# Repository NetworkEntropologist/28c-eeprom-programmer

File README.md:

# 28c-eeprom-programmer

A parallel EEPROM programmer for the 28C family, built around an Arduino Nano. Simply drop an EEPROM into the ZIF socket, connect the Nano over USB, and burn a ROM image onto it from your computer.

If you've watched Ben Eater's 8-bit computer series, this will look familiar. That's where the idea came from. I wanted a proper PCB instead of the breadboard version, and a ZIF socket so I'm not bending chip pins every time I swap an EEPROM.

## About this project

This is a personal project that I'm putting it up in case someone else finds it useful or interesting. I'm not planning to write full documentation right now, and I might not ever get to it. So for the moment, the board files and the code are the documentation.

If you find a bug, or you get it working with a chip I haven't tested, feel free to open an issue or a pull request. Just don't expect a fast reply — this is a side thing I work on when I have time.

## Where this came from

For a number of years I have been interested in retrocomputing, when one day I stumbled across [Ben Eater's YouTube channel](https://www.youtube.com/@BenEater). Following his series on espeially the [6502 breadboard computer project](https://youtube.com/playlist?list=PLowKtXNTBypFbtuVMUVXNR0z1mu7dp7eH) I wanted to start building this for myself, or rather using this as inspiration to design and build my own 6501 computer, and this EEPROM Programmer seemed like the best place to start, as this would be a required tool for pretty much everything else. 

I have to mention at this point, two other related projects that I used heavily for both inspiration, as well as for insights into how other creators tackled this:

- **Ben Eater's [eeprom-programmer](https://github.com/beneater/eeprom-programmer)** — the one from his 8-bit computer series. Same core idea as mine: an Arduino driving the address lines through a pair of 74HC595 shift registers. If you've never seen it, watch his video first. He explains the whole thing better than I can here.
- **Erik van Zijst's [eeprom](https://github.com/erikvanzijst/eeprom)** — an Arduino Uno shield with a KiCad board and an interactive Python client. Seeing someone take the breadboard version and turn it into a proper PCB with host software was a big part of what pushed me to do my own board.

So thanks to both of them. My version borrows ideas from each and mixes in what I wanted out of it.

## Does it actually work?

Short answer? Yes. First test on the PCB, after soldering it, was to attempt burning a copy of Wozmon onto the IC, which checked out byte exact. Turns out Wozmon is a really great test, as the contents is very well known and documented all over the internet.

## What it does

- Writes a ROM image to a 28C-family EEPROM over USB serial
- Reads the chip back so you can verify the write

## Supported chips

Anything in the 28C family that follows the 28C64 pinout should work. That being said, I've only tested it with a 28C64 so far. So treat everything else as *should work* rather than *known good*. If you run it with a 28C16 or 28C256, I'd like to hear how it goes.

## Hardware / BOM

The main parts, leaving out the passives:

- 1x Arduino Nano driving the entire process
- 2x 74HC595 shift registers (serial in, parallel out) driving the address lines
- 1x 28-pin ZIF socket

## Repo layout

- `hardware/` — the full KiCad project (schematic and PCB)
- `firmware/` — the Arduino firmware for the Nano
- `software/` — the host-side Python that talks to the board

## Getting boards made

The KiCad project lives in `hardware/`. Open it in KiCad, export the Gerbers, and send them off to whichever fab you like. I used JLCPCB with a purple soldermask and had no trouble — DRC passed and the boards were fine.

## Flashing the firmware

The firmware in `firmware/` was written with [PlatformIO](https://platformio.org/), not the regular Arduino IDE. So the easiest way to build and upload is with PlatformIO (either the VS Code extension or the CLI). Open the `firmware/` folder as a PlatformIO project, plug in the Nano, and run the upload.

If you're using an older Nano clone, you may need to point the build at the old bootloader, otherwise the upload will fail. That's set in the `platformio.ini`.

This assumes you've used PlatformIO before. If you haven't, their [docs](https://docs.platformio.org/) cover installing it and uploading to a board better than I could here.

## Using the software

The host software is in `software/` and it's written in Python. Fair warning: it's still very much a work in progress. Because of that I'm not going to write down a fixed set of commands here that might change next week. Have a look in the `software/` folder and read the code to see how it works for now.

I'm planning to rewrite this side in Rust later on, so expect it to change.

## License

- Hardware (everything in `hardware/`): [CERN-OHL-S v2](https://ohwr.org/cern_ohl_s_v2.txt)
- Firmware and software (`firmware/` and `software/`): [MIT](https://opensource.org/licenses/MIT)

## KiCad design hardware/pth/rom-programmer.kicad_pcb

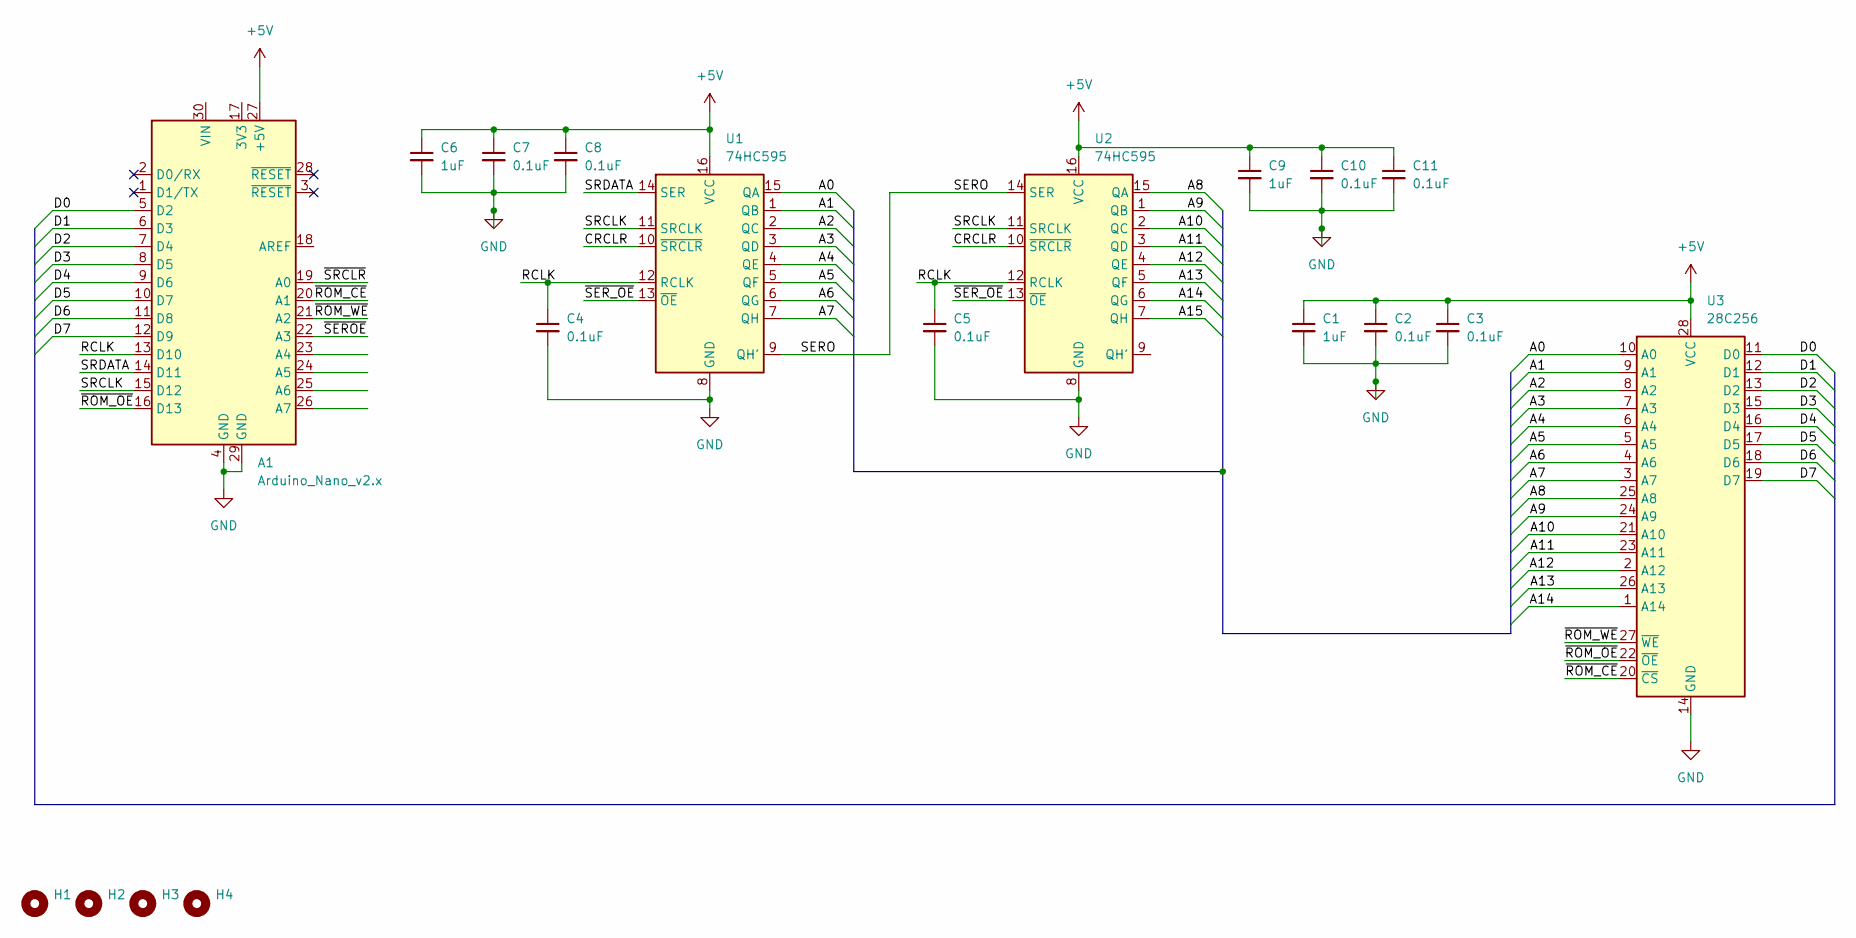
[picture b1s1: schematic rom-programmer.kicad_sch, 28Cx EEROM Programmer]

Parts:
A1: Arduino_Nano_v2.x; Arduino_Nano
C1, C6, C9: 1uF; C_Disc_D3.4mm_W2.1mm_P2.50mm; Mouser SKU 187-CL21B104KCFWPJF
C2, C3, C4, C5, C7, C8, C10, C11: 0.1uF; C_Disc_D3.4mm_W2.1mm_P2.50mm; Mouser SKU 187-CL05B104KO54PND
H1, H2, H3, H4: MountingHole; MountingHole_2.2mm_M2
U1, U2: 74HC595; DIP-16_W7.62mm_Socket; Mouser SKU 595-SN74HC595ANSR
U3: 28C256; DIP_Socket-28_W11.9mm_W12.7mm_W15.24mm_W17.78mm_W18.5mm_3M_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

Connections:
+5V: A1.27 (+5V), C1.1, C2.1, C3.1, C6.1, C7.1, C8.1, C9.1, C10.1, C11.1, U1.16 (VCC), U2.16 (VCC), U3.28 (VCC)
/A0: U1.15 (QA), U3.10 (A0)
/A1: U1.1 (QB), U3.9 (A1)
/A2: U1.2 (QC), U3.8 (A2)
/A3: U1.3 (QD), U3.7 (A3)
/A4: U1.4 (QE), U3.6 (A4)
/A5: U1.5 (QF), U3.5 (A5)
/A6: U1.6 (QG), U3.4 (A6)
/A7: U1.7 (QH), U3.3 (A7)
/A8: U2.15 (QA), U3.25 (A8)
/A9: U2.1 (QB), U3.24 (A9)
/A10: U2.2 (QC), U3.21 (A10)
/A11: U2.3 (QD), U3.23 (A11)
/A12: U2.4 (QE), U3.2 (A12)
/A13: U2.5 (QF), U3.26 (A13)
/A14: U2.6 (QG), U3.1 (A14)
/A15: U2.7 (QH)
/CRCLR: U1.10 (~SRCLR), U2.10 (~SRCLR)
/D0: A1.5 (D2), U3.11 (D0)
/D1: A1.6 (D3), U3.12 (D1)
/D2: A1.7 (D4), U3.13 (D2)
/D3: A1.8 (D5), U3.15 (D3)
/D4: A1.9 (D6), U3.16 (D4)
/D5: A1.10 (D7), U3.17 (D5)
/D6: A1.11 (D8), U3.18 (D6)
/D7: A1.12 (D9), U3.19 (D7)
/RCLK: A1.13 (D10), C4.1, C5.1, U1.12 (RCLK), U2.12 (RCLK)
/SERO: U1.9 (QH'), U2.14 (SER)
/SRCLK: A1.15 (D12), U1.11 (SRCLK), U2.11 (SRCLK)
/SRDATA: A1.14 (D11), U1.14 (SER)
/~ROM_CE: A1.20 (A1), U3.20 (~CS)
/~ROM_OE: A1.16 (D13), U3.22 (~OE)
/~ROM_WE: A1.21 (A2), U3.27 (~WE)
/~SEROE: A1.22 (A3)
/~SER_OE: U1.13 (~OE), U2.13 (~OE)
/~SRCLR: A1.19 (A0)
GND: A1.4 (GND), A1.29 (GND), C1.2, C2.2, C3.2, C4.2, C5.2, C6.2, C7.2, C8.2, C9.2, C10.2, C11.2, U1.8 (GND), U2.8 (GND), U3.14 (GND)

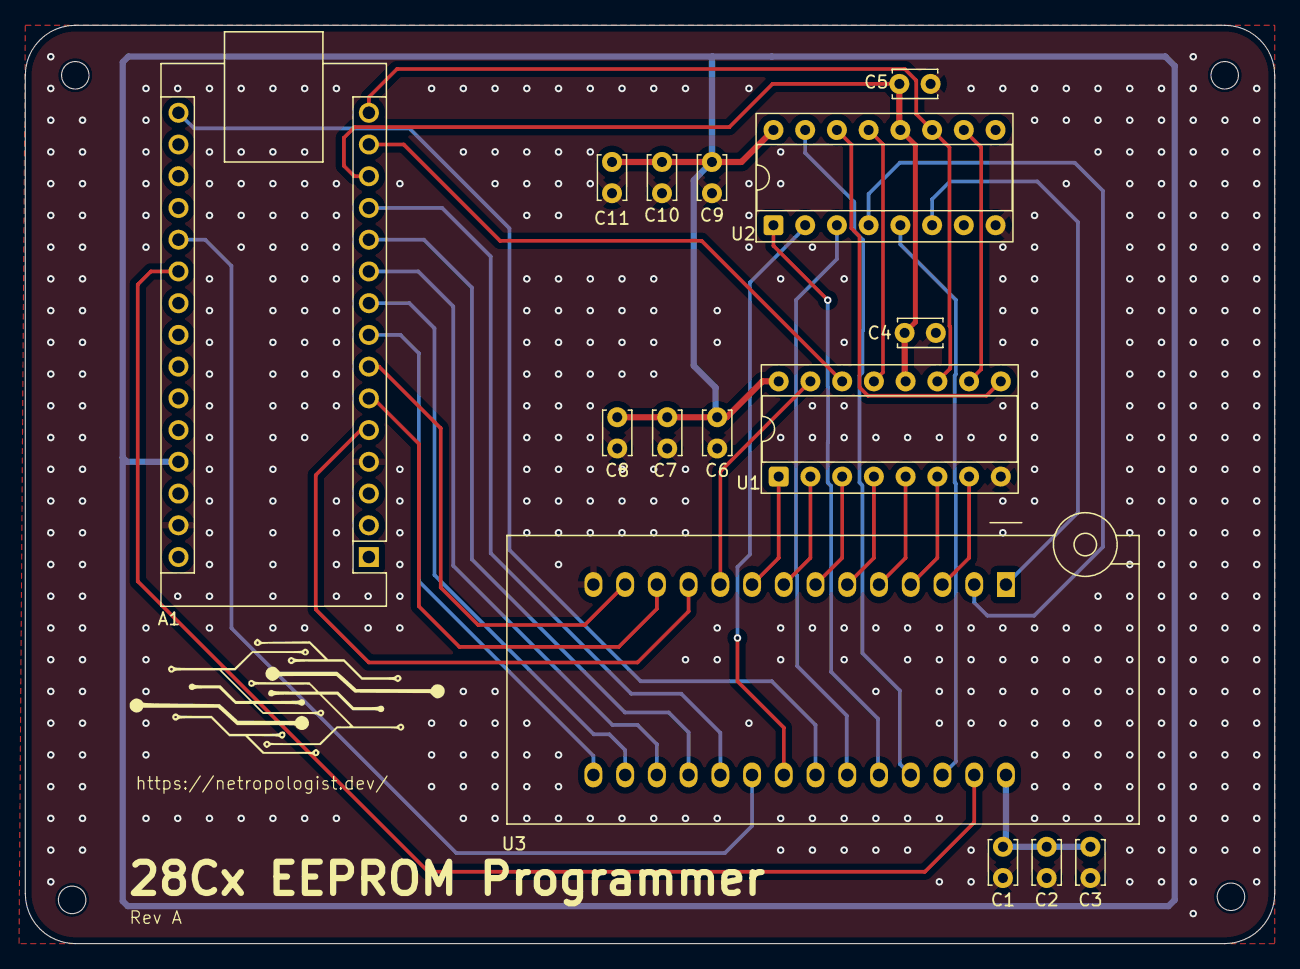
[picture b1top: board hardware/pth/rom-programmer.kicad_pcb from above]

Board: 2 copper layers, 100.0 x 73.5 mm, 19 parts (0 on the bottom side), 34 nets.

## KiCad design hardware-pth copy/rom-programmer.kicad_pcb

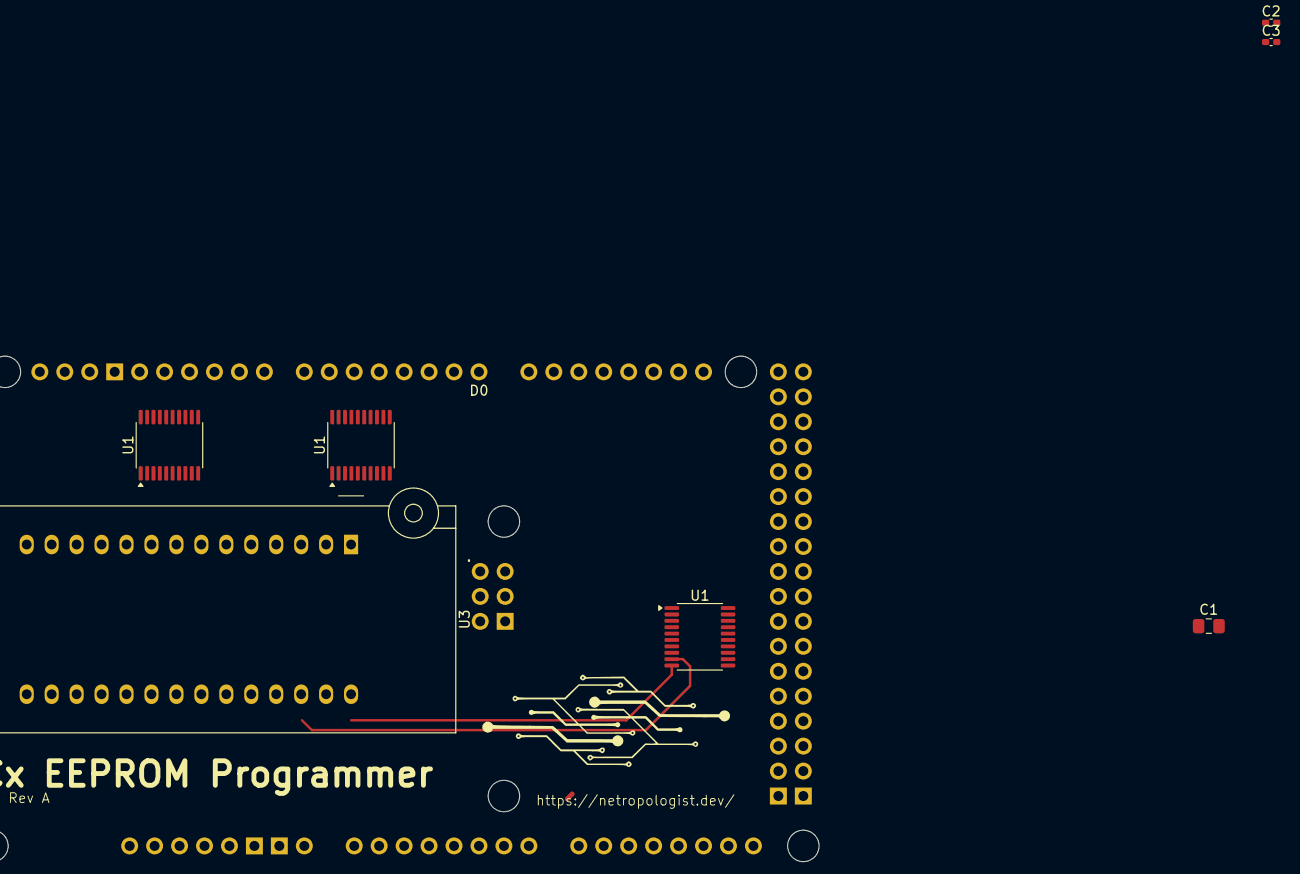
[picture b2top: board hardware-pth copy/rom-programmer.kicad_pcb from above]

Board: 2 copper layers, 8 parts (0 on the bottom side), 2 nets.

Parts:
A1: Arduino_Due_Shield
C1: 1uF; C_0805_2012Metric_Pad1.18x1.45mm_HandSolder
C2, C3: 0.1uF; C_0402_1005Metric_Pad0.74x0.62mm_HandSolder
U1, U1#2, U1#3: TXB0108PW; TSSOP-20_4.4x6.5mm_P0.65mm
U3: 28C256; DIP_Socket-28_W11.9mm_W12.7mm_W15.24mm_W17.78mm_W18.5mm_3M_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

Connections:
+5V: C1.1, C2.1, C3.1, U3.28 (VCC)
GND: C1.2, C2.2, C3.2, U3.14 (GND)

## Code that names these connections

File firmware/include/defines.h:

/**
 * @file defines.h
 * @brief Pin definitions and timing constants for 28Cx EEPROM programmer
 * @details Configure these values based on your hardware design and EEPROM requirements.
 *          Pin assignments: Update based on your Arduino connections.
 *          Timing parameters: Consult the specific EEPROM datasheet for accurate values.
 */

#ifndef DEFINES_H
#define DEFINES_H

#define ACTIVITY_LED 13 // Arduino pin D13 connected to activity LED
#define MAX_PAYLOAD 8


// EEPROM Control Pins
#define ROM_WE 14 // Arduino pin D14 (A0) connected to EEPROM /WE (active low)
#define ROM_OE 15 // Arduino pin D15 (A1) connected to EEPROM /OE (active low)
#define ROM_CE 16 // Arduino pin D16 (A2) connected to EEPROM /CE (active low)

// EEPROM Data Pins
#define D0 2 // Arduino pin D2 connected to EEPROM D0
#define D7 9 // Arduino pin D9 connected to EEPROM D7

// 74HC595 Shift Register Control Pins
#define SRCLK 12 // Arduino pin D12 connected to 74HC595 SRCLK - pin 11
#define SRCLR 17 // Arduino pin D17 (A3) connected to 74HC595 SRCLR - pin 10 (active low)
#define RCLK 10 // Arduino pin D10 connected to 74HC595 RCLK - pin 12
#define SEROE 18 // Arduino pin D18 (A4) connected to 74HC595 SEROE - pin 13 (active low)
#define DATA 11 // Arduino pin D11 connected to 74HC595 SER - pin 14

// Timing Parameters
#define WRITE_DELAY 10 // Delay in microseconds for programming operations
#define READ_DELAY 1 // Delay in microseconds for read operations
#define ADDR_DELAY 1 // Delay in microseconds for address setup
#define DATA_DELAY 1 // Delay in microseconds for data setup
#define GEN_DELAY 10 // General delay in microseconds

// More timing parameters
#define tAS 1 // Address setup time in microseconds
#define tOES 1 // Output enable setup time in microseconds
#define tAH 5 // Address hold time in microseconds
#define tWP 10 // Write pulse width in microseconds
#define tDS 5 // Data setup time in microseconds (reverted to 5)
#define tDH 5 // Data hold time in microseconds
#define tOEH 1 // Output enable hold time in microseconds
#define tCS 1 // Chip select setup time in microseconds
#define tCH 1 // Chip select hold time in microseconds
#define tDB 5 // Device busy time in microseconds
// The datasheet specifies a tWC between 200us andd 1ms. Setting this to 3ms to give a good margin for reliable
// operation, as anything lower starts introducing glitches and incorrectly written bytes.
#define tWC 300 // Write cycle time in microseconds

//#define MAX_ADDRESS 0x7FFF // Maximum address for 28C512 EEPROM (32KB)
#define MAX_ADDRESS 0x2000 // Maximum address for 28C64 EEPROM (8KB)

// Debug parameters
#define DEBUG_DATA 0xA9 // Test data value to write during address test loop
#define DEBUG_DELAY 250 // Delay in milliseconds for debugging loops to allow visual verification of blinkenlights

// Serial comms parameters
#define SERIAL_BAUD 115200 // Baud rate for serial communication with Python control script

#endif // DEFINES_H

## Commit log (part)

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2026-04-26 Updated .gitignore and VS Code workspace for PlatformIO
2026-04-26 Updated to dual license model
2026-04-27 Can now shift out addresses and set data lines.
2026-05-01 Updated .gitignore
2026-05-06 Added schematic PDF
2026-05-06 And a .svg
2026-05-06 Trigger workflow manually only
2026-05-17 Checkpoint created
2026-05-24 Serial comms finally working!
2026-05-27 Added Python S-Records library
2026-05-31 Checkpoint
2026-06-14 Can now read a single byte from the CLI
